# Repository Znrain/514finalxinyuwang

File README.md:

# 📌 514 Final Project

## 1️⃣ Project Overview
This project is designed to **measure pressure and temperature** using an **MS5837-30BA sensor** and display the results using a **stepper-motor-driven gauge needle**. The system is powered by an **ESP32-S3 microcontroller**, which processes the data and transmits it wirelessly if needed.

### **Physical Features:**
- **Sensor Device**: MS5837-30BA pressure and temperature sensor.
- **Processing Unit**: ESP32-S3 for data collection and control.
- **Display Device**: A stepper-motor-driven gauge needle for analog-style visualization.
- **Power Source**: LiPo battery for wireless operation.

**System Architecture Sketch:**  

---

## 2️⃣ Sensor Device: MS5837-30BA
The **MS5837-30BA** is a **pressure and temperature sensor** that communicates with the ESP32-S3 via the **I2C protocol**. It is used to measure environmental **pressure** and **temperature** in real-time.

### **How it Works:**
- The **sensor measures pressure** in millibars (mbar) and **temperature** in degrees Celsius (°C).
- It transmits data to the **ESP32-S3 via I2C**.
- The ESP32 processes the data and prepares it for display.

### **Sensor Diagram:**

### **Sensor Part Number:**
- **Pressure & Temperature Sensor**: MS5837-30BA  

---

## 3️⃣ Display Device: Stepper-Motor-Driven Gauge Needle
The **stepper motor with a gauge needle** provides an **analog-style display** of pressure readings. The needle moves proportionally to the measured pressure.

### **How it Works:**
- The **ESP32-S3** sends control signals to the **motor driver**.
- The **stepper motor rotates** to move the gauge needle.
- The **needle position** corresponds to the measured pressure.
- The **display updates in real-time**.

### **Display Diagram:**

### **Display Components & Part Numbers:**
- **Stepper Motor**: X25-589  
- **Motor Driver**: SP_X27_e_C  

---

## 4️⃣ System Communication & Detailed Diagram
The **ESP32-S3** acts as the central unit, reading sensor data, processing it, and sending commands to the display.

### **Communication Flow:**
1. **MS5837-30BA sensor** measures pressure and temperature.
2. The sensor **sends data via I2C** to the ESP32-S3.
3. The **ESP32 processes the data** and converts it into a stepper motor signal.
4. The **motor driver (SP_X27_e_C) moves the gauge needle** to display pressure.
5. Optional: **Wireless transmission** can be added using **ESP32's 2.4GHz antenna**.

### **System Diagram:**
**Device Communication Chart**:  

---

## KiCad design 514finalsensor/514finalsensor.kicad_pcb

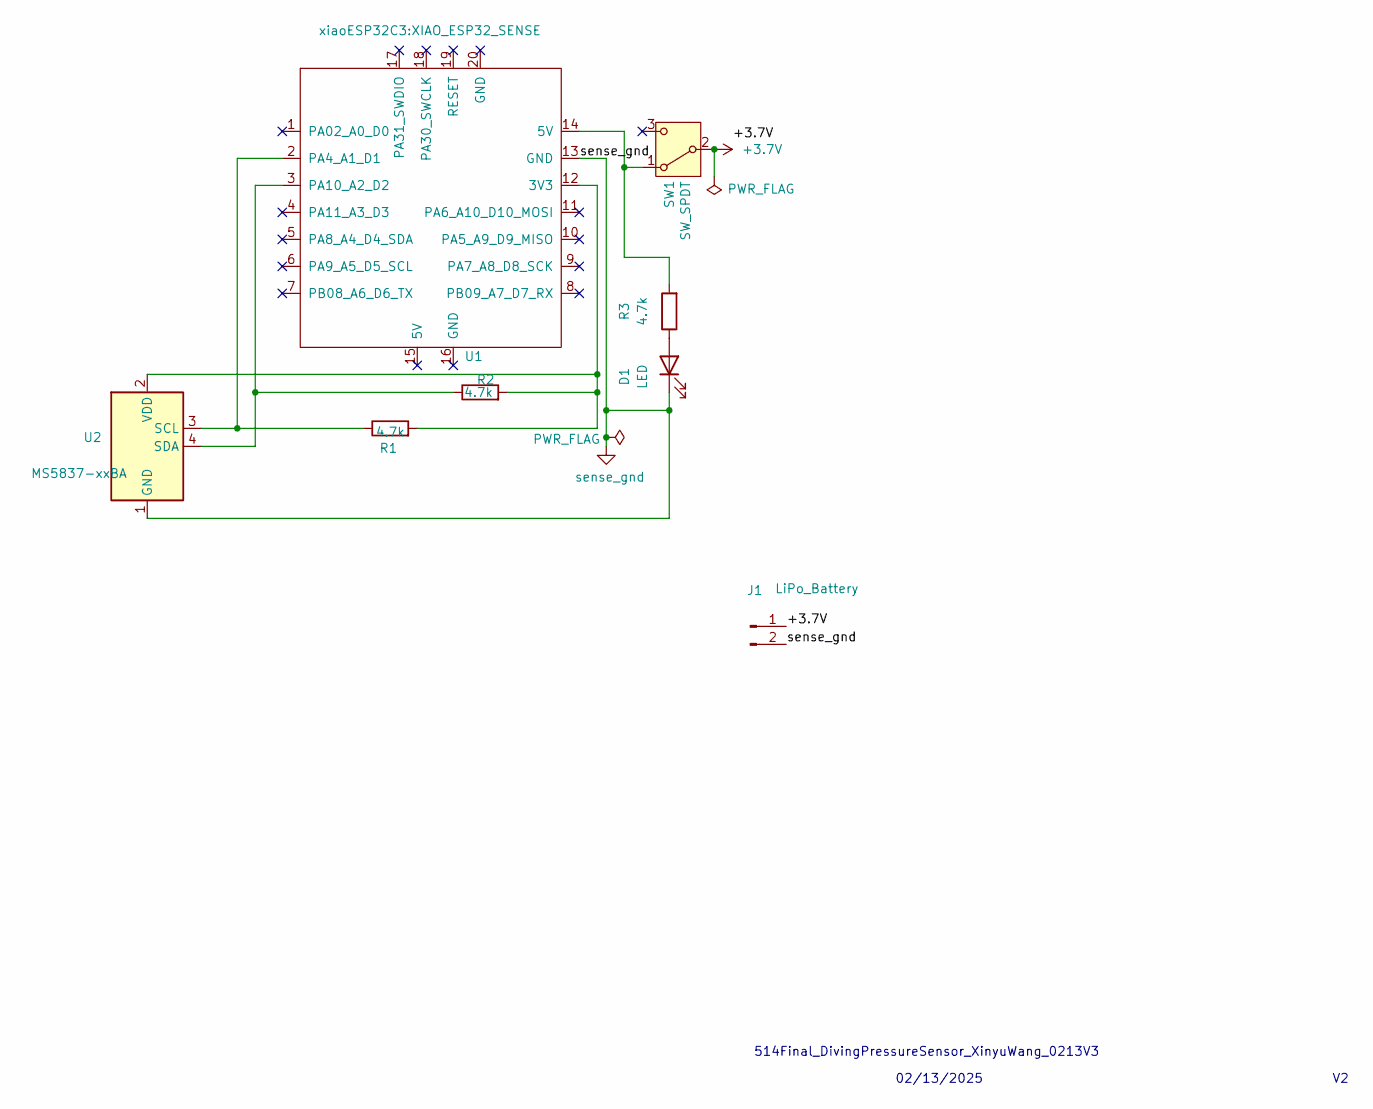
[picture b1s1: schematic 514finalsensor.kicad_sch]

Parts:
D1: LED; LED_D3.0mm
J1: LiPo_Battery; JST_PH_B2B-PH-K_1x02_P2.00mm_Vertical
R1, R2, R3: 4.7k; R_0805_2012Metric_Pad1.20x1.40mm_HandSolder
SW1: SW_SPDT; PinHeader_1x03_P2.54mm_Vertical
U1: SeeeduinoXIAO; XIAO_ESP32_SENSE
U2: MS5837-xxBA; PinHeader_1x04_P2.54mm_Vertical

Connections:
+3.7V: J1.1, SW1.2 (B)
unnamed: D1.2 (A), R3.1
unnamed: R3.2, SW1.1 (A), U1.14 (5V)
unnamed: R1.2, R2.2, U1.12 (3V3), U2.2 (VDD)
unnamed: R1.1, U1.2 (PA4_A1_D1), U2.3 (SCL)
unnamed: R2.1, U1.3 (PA10_A2_D2), U2.4 (SDA)
sense_gnd: D1.1 (K), J1.2, U1.13 (GND), U2.1 (GND)

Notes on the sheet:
514Final_DivingPressureSensor_XinyuWang_0213V3
02/13/2025

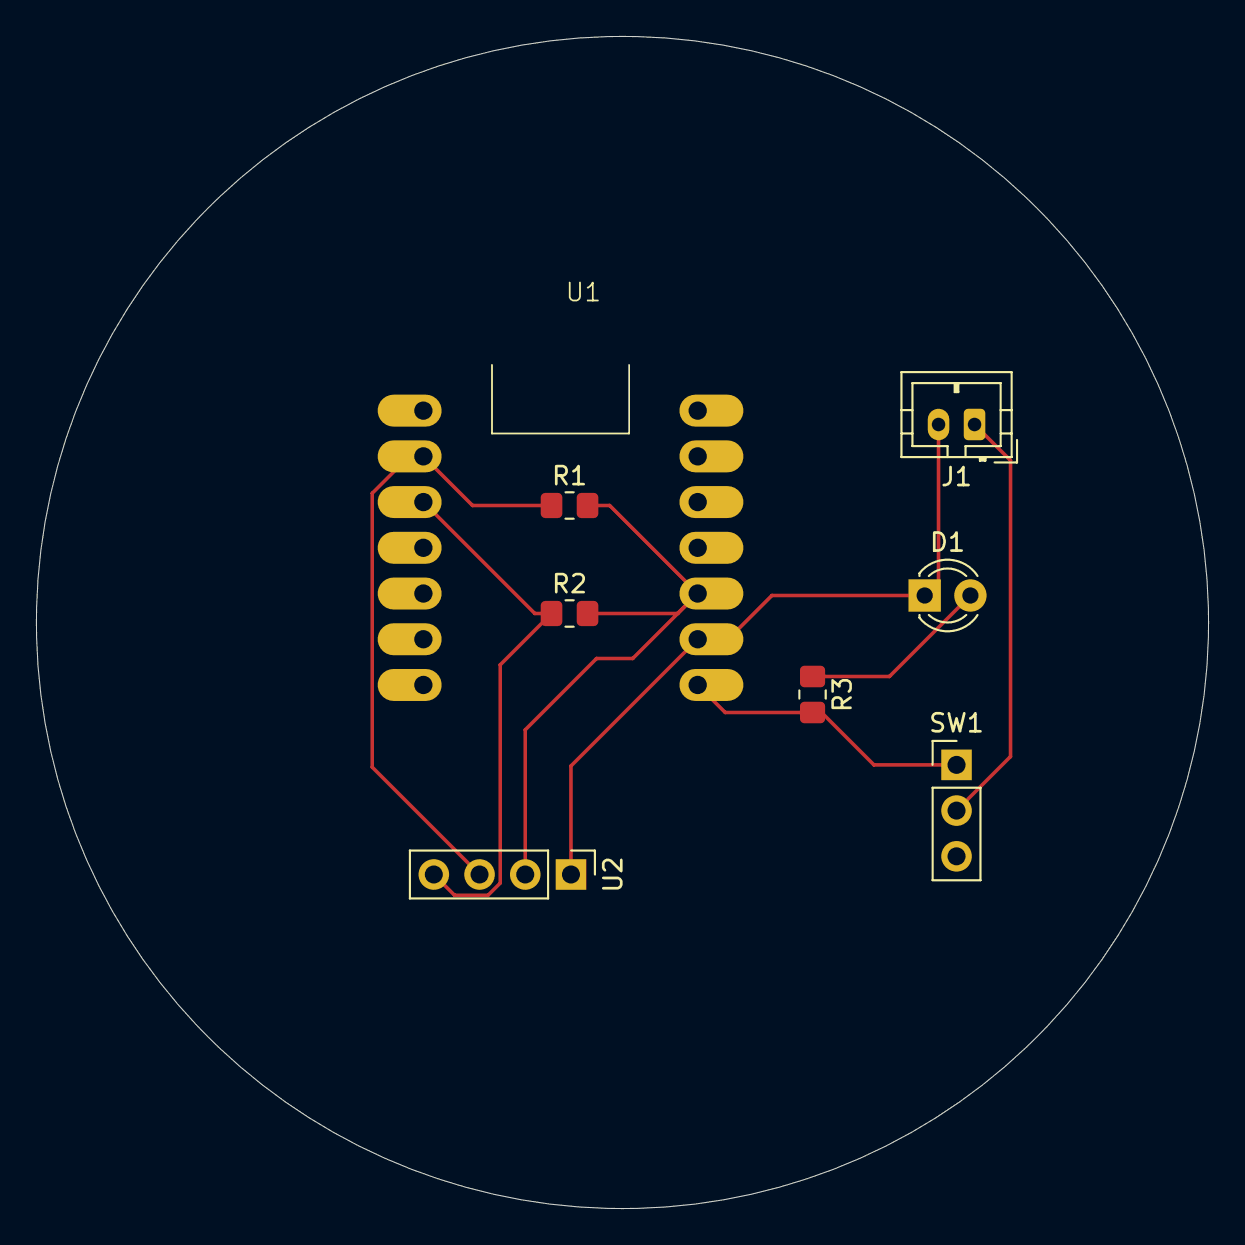
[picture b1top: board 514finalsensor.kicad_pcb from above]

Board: 2 copper layers, 65.1 x 65.1 mm, 8 parts (0 on the bottom side), 7 nets.

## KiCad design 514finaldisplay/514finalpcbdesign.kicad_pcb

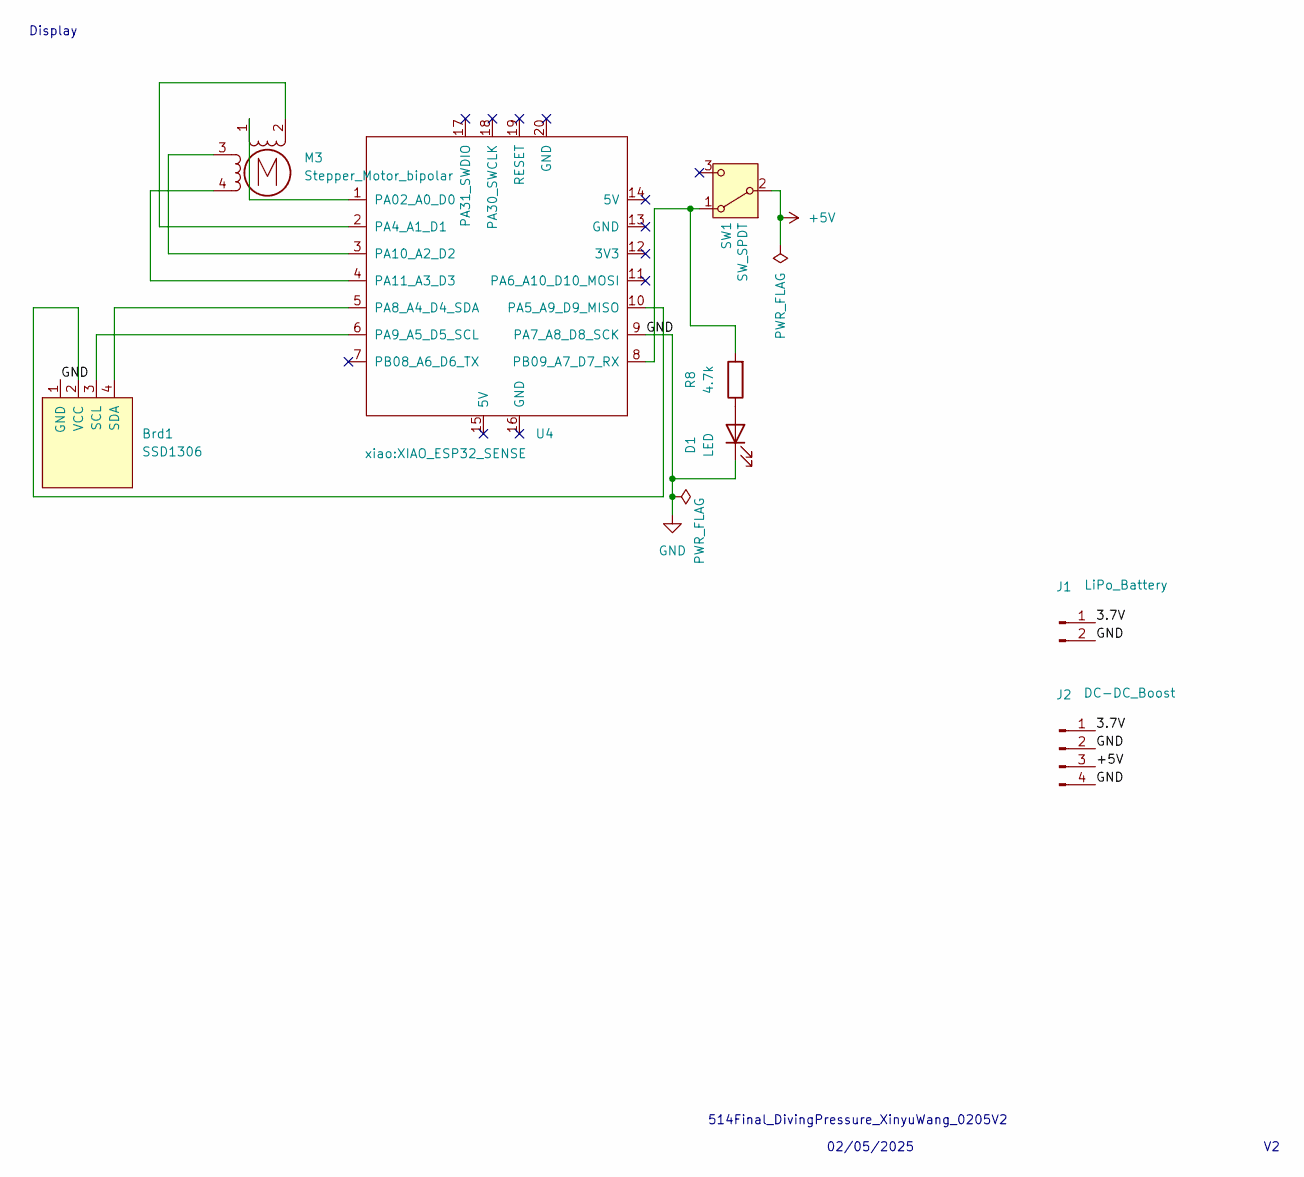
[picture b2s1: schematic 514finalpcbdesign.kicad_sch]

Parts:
Brd1: SSD1306; 128x64OLED
D1: LED; LED_D3.0mm
J1: LiPo_Battery; JST_PH_B2B-PH-K_1x02_P2.00mm_Vertical
J2: DC-DC_Boost; PinHeader_1x04_P2.54mm_Vertical
M3: Stepper_Motor_bipolar; x27_stepper_two_holes
R8: 4.7k; R_0805_2012Metric_Pad1.20x1.40mm_HandSolder
SW1: SW_SPDT; PinHeader_1x03_P2.54mm_Vertical
U4: SeeeduinoXIAO; XIAO_ESP32_SENSE

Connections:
+5V: J2.3, SW1.2 (B)
/3.7V: J1.1, J2.1
GND: Brd1.1 (GND), D1.1 (K), J1.2, J2.2, J2.4, U4.9 (PA7_A8_D8_SCK)
unnamed: Brd1.3 (SCL), U4.6 (PA9_A5_D5_SCL)
unnamed: Brd1.4 (SDA), U4.5 (PA8_A4_D4_SDA)
unnamed: Brd1.2 (VCC), U4.10 (PA5_A9_D9_MISO)
unnamed: D1.2 (A), R8.1
unnamed: M3.2 (-), U4.2 (PA4_A1_D1)
unnamed: R8.2, SW1.1 (A), U4.8 (PB09_A7_D7_RX)
unnamed: M3.1, U4.1 (PA02_A0_D0)
unnamed: M3.3, U4.3 (PA10_A2_D2)
unnamed: M3.4, U4.4 (PA11_A3_D3)

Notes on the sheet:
514Final_DivingPressure_XinyuWang_0205V2
Display
02/05/2025

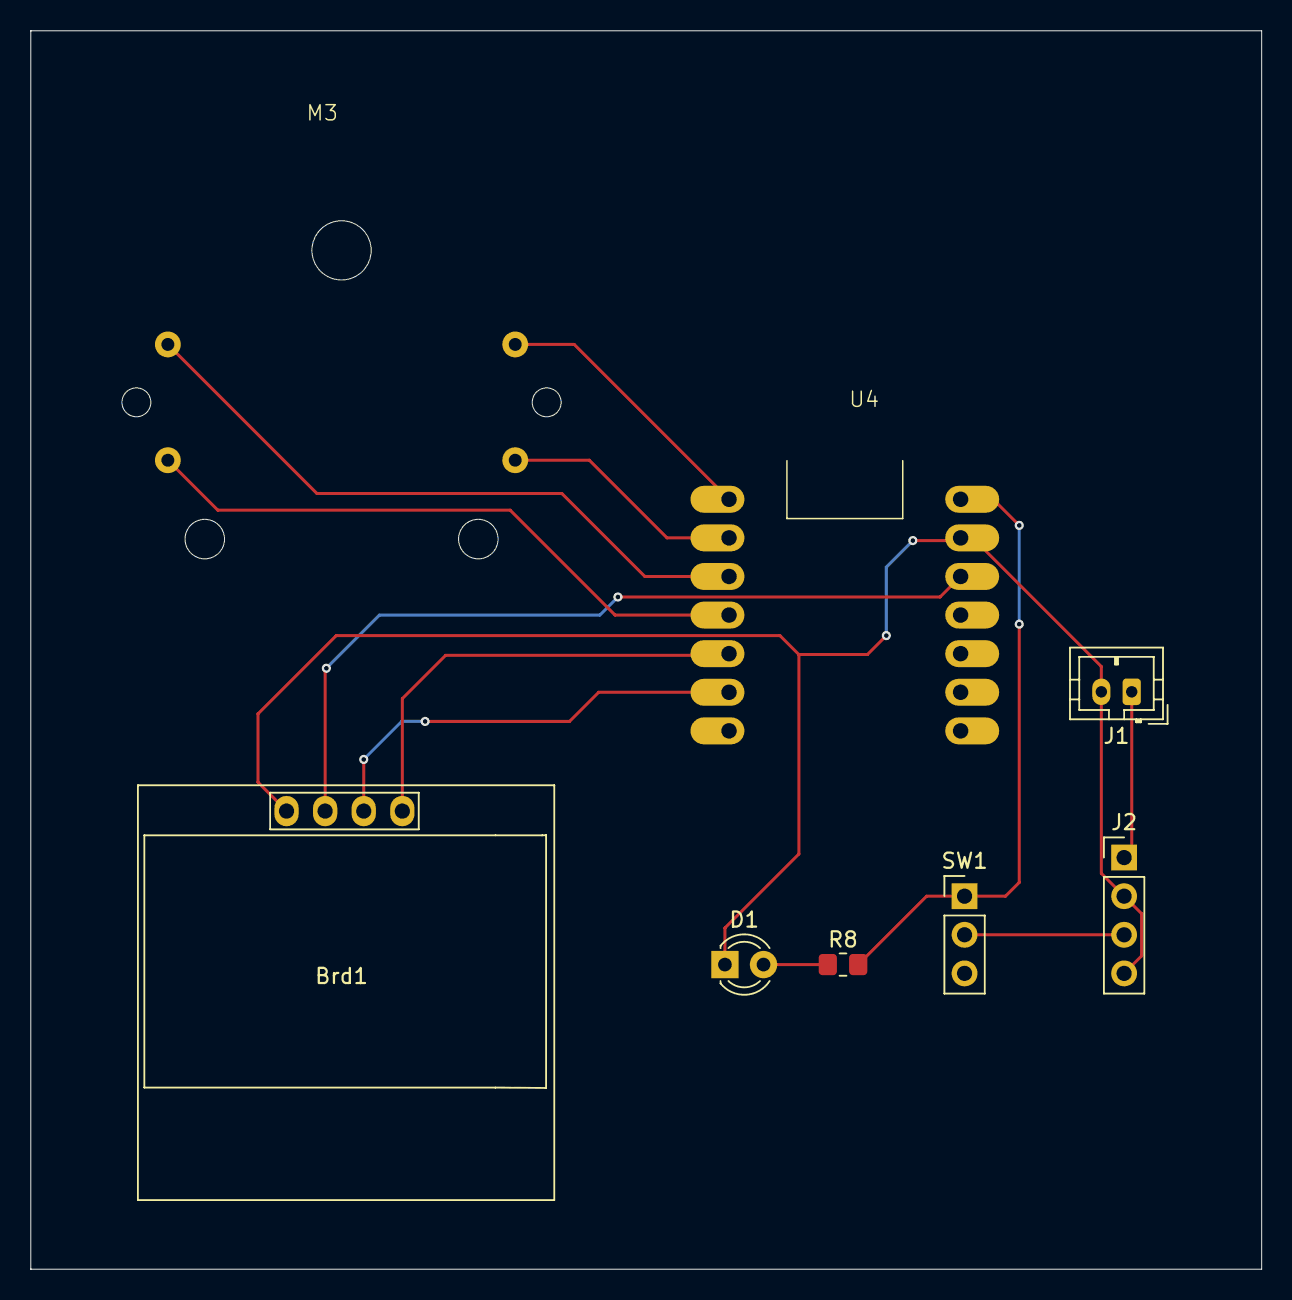
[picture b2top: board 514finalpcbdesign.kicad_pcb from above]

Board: 2 copper layers, 81.0 x 81.5 mm, 8 parts (0 on the bottom side), 12 nets.

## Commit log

2025-01-20 Initial commit for final project
2025-01-20 Add README file
2025-01-20 Add sensor and display device descriptions
2025-01-20 Added datasheets for ESP32-S3, MS5837-30BA, stepper motor, and driver
2025-01-20 Added images folder with architecture and sensor/display images
2025-01-20 Added README with system architecture and images
2025-01-28 Initial commit - Add KiCAD project
2025-03-12 Add PCB, display and sensor files for final project
